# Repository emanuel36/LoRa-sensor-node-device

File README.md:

<h3 align="center">A low cost and low power LoRa device sensor-node</h3>

[![Version][release-shield]][release-url]
[![commits-shield][commits-shield]][commits-url]
[![Stargazers][stars-shield]][stars-url]
![language-shield]
![Size][size-shield]
 
 <p align="center">
    <br />
    <a href="https://github.com/emanuel36/LoRa-sensor-node-device//tree/master/documentation"><strong>:page_facing_up: Explore the documentation :page_facing_up:</strong></a>
    <br />
    <a href="https://github.com/emanuel36/LoRa-sensor-node-device/issues">:warning: Report or Suggest Something :warning:</a>
  </p>
</p>

<br />
<p align="center">

## Table of Contents

* [About the Project](#about-the-project)
  * [Built With](#built-with)
* [Detailed description](#detailed-description)
  * [Components Specifications](#components-specifications)
  * [Schematic](#schematic)
  * [Board](#board) 
* [Assembled Board With Components](#assembled-board-with-components)
* [Contact](#contact)

## About The Project

This is a project of a new LoRa device sensor-node. This device is capable of collecting environment data such as temperature, humidity, soil moisture and ambient as well as sending all data to a LoRa gateway from miles away. As can be seen from the [component specifications](#components-specifications) table, this device is very inexpensive, therefore it is suitable equipment to apply to a wireless sensor network in an agricultural field.

More details can be seen in this [publication](https://www.embarcados.com.br/dispositivo-sensor-no-lora-de-baixo-custo-utilizando-energia-solar/) (Portuguese language).

### Built With
* [LoRa](https://lora-alliance.org/)
* [PIC16F18426](https://www.microchip.com/wwwproducts/en/PIC16F18426)
* [MPLAP X IDE](https://www.microchip.com/mplab/mplab-x-ide)

### IDE and Compiler Version
* [MPLAB XC8 v2.10](https://www.microchip.com/development-tools/pic-and-dspic-downloads-archive)
* [MPLAP X IDE v5.30](https://www.microchip.com/development-tools/pic-and-dspic-downloads-archive)

## Detailed Description
This device is designed to work automatically without any human intervention. 

### Microcontroller
The PIC16F18426 is perfect for the project, it's a family of Microchip MCUs intended to sensor node devices.

### Sensors
The device has 4 sensors to measure air temperature, ground temperature, air humidity, soil moisture and sunlight or light levels.

### LoRa Transmitter
The cheap SX1276 transmitter works well at a frequency of 915 MHz, because I'm using it in Brazil.

### Power Supply System
The electrical and power system is designed for decades of operation, with a combination of a large rechargeable battery and a solar-powered recharge system. It is possible to use this device only with solar energy without battery, the battery is only for power supply when there is no sunlight, such as at night and cloudy days.

### Power-Saving Operation Mode
Most of the time the device remains in power save state with all peripherals turned off. When it is necessary to perform some task the system is woken up by an interruption. The data send and transmit period can be set between 5 and 80 minutes, so the system is woken up by a timer interrupt, performs the tasks and returns to power save mode.

### Status LED
The device can signal its current status through a flashing blue LED when it is operating normally and red when something is wrong such as low battery, sensor reading failure or incorrect sensor data such as 80ºC temperature.

### Components specifications

| Component   | Description/Documentation   | Price (USD)   |
|---------------------------------  |:-----------------------------------------------------------------------------------------------------------------------------------------:  |------------:  |
| Microcontroller   | [PIC16F18426](https://www.microchip.com/wwwproducts/en/PIC16F18426)   | $1,02   |
| LoRa Transmiter   | [SX1276](https://www.semtech.com/products/wireless-rf/lora-transceivers/sx1276) | $4,15   |
| Solar Panel   | [Wavgat solar panel 1W/5V](https://pt.aliexpress.com/item/32844672794.html?isOrigTitle=true)  | $1,31   |
| LED | [RGB LED](https://www.sparkfun.com/datasheets/Components/YSL-R596CR3G4B5C-C10.pdf)  | $0,10 |
| Voltage regulator   | [LM2596](http://www.ti.com/product/LM2596)  | $0,30   |
| Switch   | [DIP Switch 1 way](https://www.we-online.de/katalog/datasheet/418117270901.pdf)  | $0,16 |
| PINS | [Header pin male](https://cdn.sparkfun.com/datasheets/Prototyping/16188.pdf)  | $0,20  |
| MCU Socket | [14-PIN PDIP Socket](https://www.sparkfun.com/products/7939)  | $0,50   |
| 10k Resistors  | [10k Resistors](https://www.circuitspecialists.com/rb10k.html) | $0,12 |
| 4.7k Resistor  | [4.7k Resistors](https://www.circuitspecialists.com/ra4.7k.html) | $0,05 |
| Battery   | [Panasonic NCR18650B](https://www.batteryspace.com/prod-specs/NCR18650B.pdf)  | $4,75   |
| Battery Holder  | [BK-18650-PC2](http://www.memoryprotectiondevices.com/datasheets/BK-18650-PC2-datasheet.pdf)  | $0,49   |
| Light Sensor  | [MAX44009](https://www.maximintegrated.com/en/products/interface/sensor-interface/MAX44009.html)  | $1,55   |
| Air Temperature/Humidity Sensor   | [Sensirion SHT30](https://www.sensirion.com/en/environmental-sensors/humidity-sensors/digital-humidity-sensors-for-various-applications/)   | $1,90   |
| Soil Moisture Sensor  | [Capacitive soil moisture sensor v1.2](https://media.digikey.com/pdf/Data%20Sheets/DFRobot%20PDFs/SEN0193_Web.pdf)  | $0,76   |
| Soil Temperature  | [DS18B20](https://www.maximintegrated.com/en/products/DS18B20)  | $1,00   |
|**Total** |-| **$18,36**|

### Schematic

### Board

## Assembled Board With Components

## System Running

## Data collected

## Acknowledgements

I would like to thank all the professors I've had since elementary school, this project is the result of a combination of everything you taught me.

The SX1276 LoRa transmitter driver was adapted from https://github.com/sandeepmistry/arduino-LoRa.

[contributors-shield]: https://img.shields.io/github/contributors/emanuel36/LoRa-sensor-node-device?style=for-the-badge
[commits-shield]:https://img.shields.io/github/last-commit/emanuel36/LoRa-sensor-node-device?style=for-the-badge
[commits-url]:https://github.com/emanuel36/LoRa-sensor-node-device/commits/master
[release-shield]:https://img.shields.io/github/v/release/emanuel36/LoRa-sensor-node-device?style=for-the-badge
[release-url]:https://github.com/emanuel36/LoRa-sensor-node-device/releases
[contributors-url]: https://github.com/emanuel36/LoRa-sensor-node-device/graphs/contributors
[stars-shield]: https://img.shields.io/github/stars/emanuel36/LoRa-sensor-node-device?color=183c0d&style=for-the-badge
[stars-url]: https://github.com/emanuel36/LoRa-sensor-node-device/stargazers
[language-shield]: https://img.shields.io/github/languages/top/emanuel36/LoRa-sensor-node-device?color=191970&style=for-the-badge
[language-url]: https://github.com/emanuel36/LoRa-sensor-node-device/search?l=c
[size-shield]: https://img.shields.io/github/languages/code-size/emanuel36/LoRa-sensor-node-device?color=008080&style=for-the-badge
[issues-shield]: https://img.shields.io/github/issues/emanuel36/LoRa-sensor-node-device?style=for-the-badge
[issues-url]:https://github.com/emanuel36/LoRa-sensor-node-device/issues
[linkedin-shield]: https://img.shields.io/badge/-LinkedIn-blue?style=for-the-badge
[linkedin-url]: https://www.linkedin.com/in/emanuel36/en

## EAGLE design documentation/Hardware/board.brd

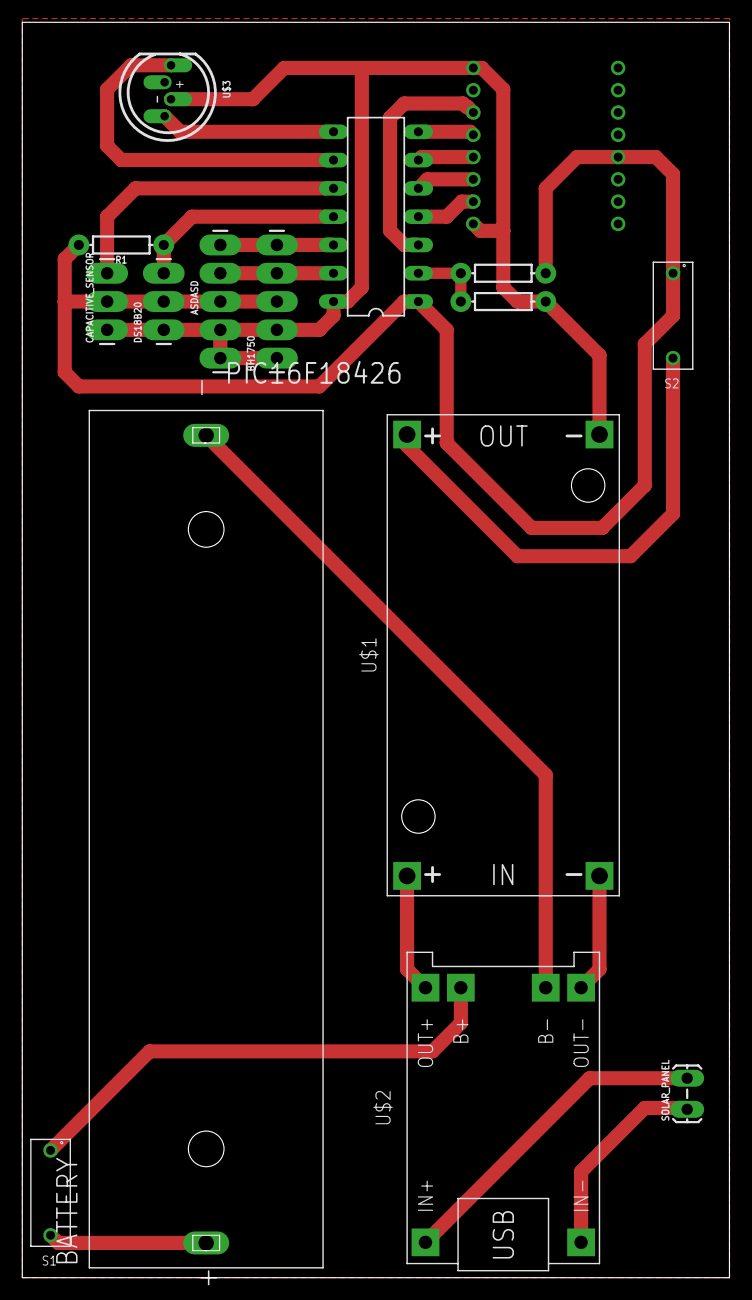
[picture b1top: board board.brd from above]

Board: 2 copper layers, 63.5 x 112.7 mm, 16 parts (1 on the bottom side), 22 nets.

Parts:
ASDASD: 1X05_LONGPADS
BATTERY: BK-18650-PC2; MPD_BK-18650-PC2
BH1750: 1X05_LONGPADS
CAPACITIVE_SENSOR: 1X03_LONGPADS
DS18B20: 1X03_LONGPADS
PIC16F18426: PIC16F8DIL; DIL14
R1: 1k; AXIAL-0.3
R2, R3: 1M; AXIAL-0.3
S1, S2: 418117270901
SOLAR_PANEL: 1X02_LOCK_LONGPADS
SX1276-RF: WIRELESS-LORA-RFM95W#THT
U$1: DC-DC-STEP-DOWN-LM2596
U$2: BATTERY-CHARGER-LI-PROT
U$3: WS2812B-PTH; WS2812B-PTH-KIT

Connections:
B-: BATTERY.M, U$2.B-
GND: ASDASD.1, ASDASD.2, BH1750.1, BH1750.2, CAPACITIVE_SENSOR.1, DS18B20.1, PIC16F18426.14, R3.P$2, SX1276-RF.A1, SX1276-RF.A8, U$1.OUT-, U$3.2
unnamed: U$1.IN+, U$2.OUT+
unnamed: SOLAR_PANEL.1, U$2.IN-
unnamed: BATTERY.P, S1.A1
unnamed: U$1.IN-, U$2.OUT-
unnamed: SOLAR_PANEL.2, U$2.IN+
RA0: ASDASD.4, BH1750.4, PIC16F18426.13
RA1: ASDASD.5, BH1750.5, PIC16F18426.12
RA2: DS18B20.3, PIC16F18426.11, R1.P$1
RA3: PIC16F18426.4, SX1276-RF.A2
RA4: PIC16F18426.3, SX1276-RF.A6
RA5: PIC16F18426.2, R2.P$1, R3.P$1
RC0: CAPACITIVE_SENSOR.3, PIC16F18426.10
RC1: PIC16F18426.9, U$3.4
RC2: PIC16F18426.8, U$3.1
RC3: PIC16F18426.7, SX1276-RF.A5
RC4: PIC16F18426.6, SX1276-RF.A4
RC5: PIC16F18426.5, SX1276-RF.A3
SB: S1.1, U$2.B+
SS: S2.A1, U$1.OUT+
VCC: ASDASD.3, BH1750.3, CAPACITIVE_SENSOR.2, DS18B20.2, PIC16F18426.1, R1.P$2, R2.P$2, S2.1, SX1276-RF.B4

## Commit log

2019-09-23 MCC config - Led Blink
2019-09-24 UART for debug
2019-09-24 i2c - mssp1
2019-09-24 sht30 driver
2019-09-24 sht30 driver error detection
2019-09-24 max44009 lightness sensor driver
2019-09-24 battery voltage monitor
2019-09-27 Logical folders MPLAB
2019-09-27 Folder rename
2019-09-28 Timer0 Interrupt - 5 Minutes
2019-09-28 Handler Interrupt bug fix
2019-09-28 battery
2019-09-28 ds18b20 and oneWire protocol
2019-09-28 Sleep mode
2019-09-29 Timer2 and Led Status
2019-09-29 eusart bug correction
2019-09-30 i2c bug correction
2019-10-01 Readme.md updated
2019-10-01 Readme.md update
2019-10-02 rename repository
2019-10-03 ADC bug fix
2019-10-08 sensors running together
2019-10-08 soil moisture capcitive sensor
2019-10-08 Include Directory Path
2019-10-08 Project configurations
2019-10-09 documentation
2019-10-09 spi drivers
2019-10-09 Update issue templates
2019-10-09 readme.md
2019-10-13 spi bug fixed
2019-10-30 add board to readme.md
2019-10-31 board img update
2019-11-07 several adjusts specially in SPI protoco
2019-11-16 several changes for bluetooth version board
2019-11-22 changes for add sx1276 lora transmiter
2019-11-22 SX1276 LoRaWAN transceiver added
2019-11-22 reading data and sending by LoRaWAN transmiter
2019-11-22 readme.md updates
2019-11-23 soil moisture sensor calibrated
2019-11-23 description update
2019-11-23 main update
2019-11-25 Board photos
2019-11-25 foto
2019-11-25 some adjusts
2019-11-26 new photo
2019-12-02 new files
2019-12-02 folder renamed
2019-12-02 photo changed
2019-12-07 Set theme jekyll-theme-slate

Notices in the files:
parts and their libraries:
SparkFun-Connectors: Licensing: Creative Commons ShareAlike 4.0 International - https://creativecommons.org/licenses/by-sa/4.0
diy-modules: Released under the Creative Commons Attribution 4.0 International License: http://creativecommons.org/licenses/by/4.0
